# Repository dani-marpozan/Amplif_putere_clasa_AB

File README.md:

# Amplificator in clasa AB 

Model 3D

## Schematic

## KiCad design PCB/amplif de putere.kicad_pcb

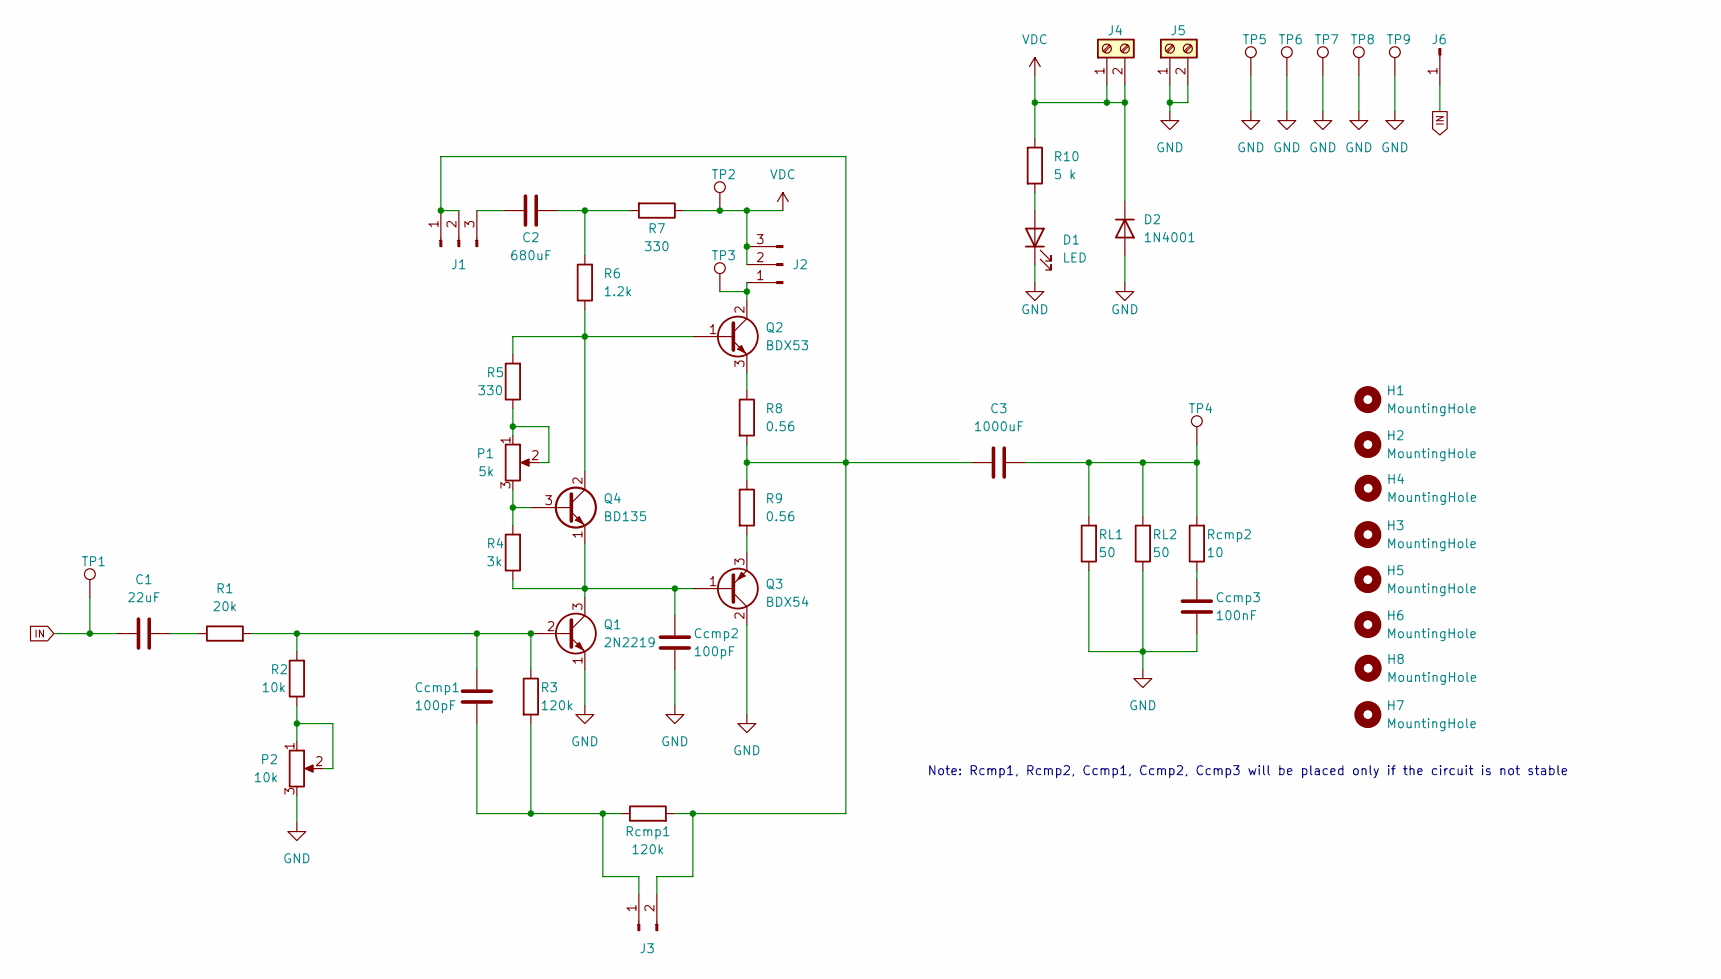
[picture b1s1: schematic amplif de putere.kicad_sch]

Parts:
C1: 22uF; C_Radial_D5.0mm_H11.0mm_P2.00mm
C2: 680uF; C_Radial_D10.0mm_H20.0mm_P5.00mm
C3: 1000uF; C_Radial_D10.0mm_H16.0mm_P5.00mm
Ccmp1, Ccmp2: 100pF; C_Disc_D3.0mm_W2.0mm_P2.50mm
Ccmp3: 100nF; C_Disc_D6.0mm_W2.5mm_P5.00mm
D1: LED; LED_D5.0mm
D2: 1N4001; D_DO-41_SOD81_P10.16mm_Horizontal
H1, H2, H3, H4: MountingHole; MountingHole_3.2mm_M3_ISO7380_Pad_TopBottom
H5, H6, H7, H8: MountingHole; MountingHole_3.2mm_M3
J1, J2: Conn_01x03_Male; PinHeader_1x03_P2.54mm_Vertical
J3: Conn_01x02_Male; PinHeader_1x02_P2.54mm_Vertical
J4, J5: Screw_Terminal_01x02; TerminalBlock_Phoenix_MKDS-1,5-2_1x02_P5.00mm_Horizontal
J6: Conn_01x01_Male; TestPoint
P1: 5k; Custom Potentiometer footprint
P2: 10k; Custom Potentiometer footprint
Q1: 2N2219; TO-39-3
Q2: BDX53; TO-220-3_Vertical
Q3: BDX54; TO-220-3_Vertical
Q4: BD135; TO-126-3_Vertical
R1: 20k; R_Axial_DIN0207_L6.3mm_D2.5mm_P10.16mm_Horizontal
R2: 10k; R_Axial_DIN0207_L6.3mm_D2.5mm_P10.16mm_Horizontal
R3: 120k; R_Axial_DIN0207_L6.3mm_D2.5mm_P10.16mm_Horizontal
R4: 3k; R_Axial_DIN0207_L6.3mm_D2.5mm_P10.16mm_Horizontal
R5, R7: 330; R_Axial_DIN0207_L6.3mm_D2.5mm_P10.16mm_Horizontal
R6: 1.2k; R_Axial_DIN0207_L6.3mm_D2.5mm_P10.16mm_Horizontal
R8, R9: 0.56; R_Axial_DIN0516_L15.5mm_D5.0mm_P20.32mm_Horizontal
R10: 5 k; R_Axial_DIN0207_L6.3mm_D2.5mm_P10.16mm_Horizontal
RL1, RL2: 50; Power resistor 50R
Rcmp1: 120k; R_Axial_DIN0207_L6.3mm_D2.5mm_P10.16mm_Horizontal
Rcmp2: 10; R_Axial_DIN0207_L6.3mm_D2.5mm_P10.16mm_Horizontal
TP1, TP2, TP3, TP4: TestPoint; Kesytone TP Multipurpose 5013
TP5, TP6, TP7, TP8, TP9: TestPoint

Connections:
GND: Ccmp2.1, Ccmp3.1, D1.1 (K), D2.2 (A), J5.1, J5.2, P2.3, Q1.1 (E), Q3.2 (C), RL1.1, RL2.1, TP5.1, TP6.1, TP7.1, TP8.1, TP9.1
IN: C1.1, J6.1, TP1.1
unnamed: C1.2, R1.1
unnamed: C2.1, R6.2, R7.2
unnamed: C3.2, RL1.2, RL2.2, Rcmp2.2, TP4.1
unnamed: Ccmp3.2, Rcmp2.1
unnamed: D1.2 (A), R10.2
unnamed: C3.1, J1.1, J1.2, J3.2, R8.2, R9.1, Rcmp1.2
unnamed: C2.2, J1.3
unnamed: J2.1, Q2.2 (C), TP3.1
unnamed: Ccmp1.1, J3.1, R3.2, Rcmp1.1
unnamed: P1.1, P1.2, R5.1
unnamed: P2.1, P2.2, R2.1
unnamed: Ccmp1.2, Q1.2 (B), R1.2, R2.2, R3.1
unnamed: Ccmp2.2, Q1.3 (C), Q3.1 (B), Q4.1 (E), R4.1
unnamed: Q2.1 (B), Q4.2 (C), R5.2, R6.1
unnamed: Q2.3 (E), R8.1
unnamed: Q3.3 (E), R9.2
unnamed: P1.3, Q4.3 (B), R4.2
VDC: D2.1 (K), J2.2, J2.3, J4.1, J4.2, R7.1, R10.1, TP2.1

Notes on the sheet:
Note: Rcmp1, Rcmp2, Ccmp1, Ccmp2, Ccmp3 will be placed only if the circuit is not stable

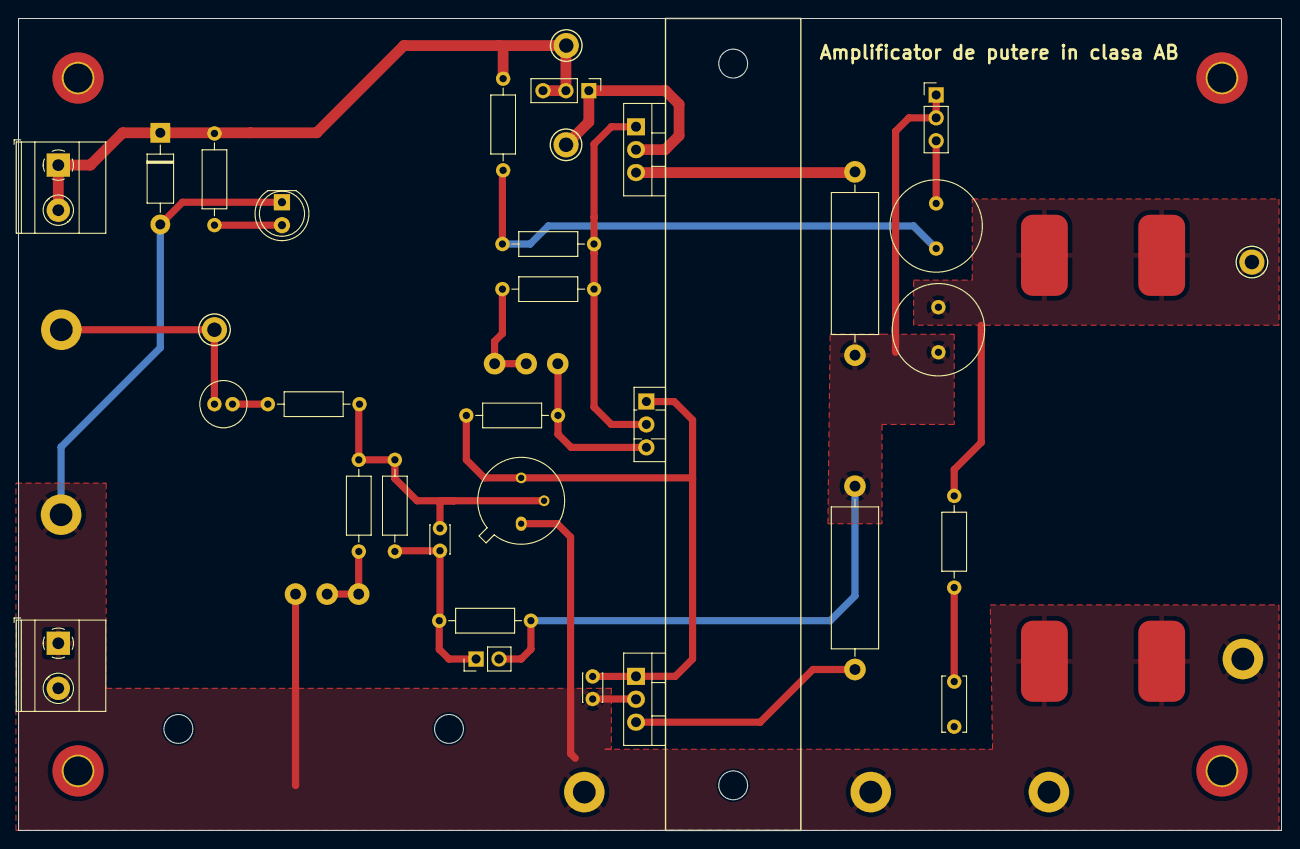
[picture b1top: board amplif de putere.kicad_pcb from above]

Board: 2 copper layers, 140.0 x 90.0 mm, 51 parts (0 on the bottom side), 20 nets.
